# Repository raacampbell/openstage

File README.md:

<h1>OpenStage</h1>
<i>Open source microscope stage controller</i>
<br />

OpenStage is a hardware and software solution for cheaply motorizing a microscope stage. The system is accurate enough even for demanding tasks, such as fine focus operations on a 2-photon microscope. The characteristics of the system and important build information are described in our <a href="http://www.plosone.org/article/info%3Adoi%2F10.1371%2Fjournal.pone.0088977">PlosONE paper</a>. We achieved absolute unidirectional positioning accuracy and repeatability better than 0.1 μm in Z. Bidirectional positioning accuracy is in the range of 0.5 μm to 0.75 μm in Z. Positioning repeatability in X and Y is better than 1 μm. Minimum incremental motion is 0.04 μm in Z and 0.1 μm in X and Y. These values compare favorably to many commercial actuators costing several times as much as our system.

Our system costs roughly $1000 for three axes (controller + motors + motor coupling hardware). Up to four axes are possible. Commercial solutions cost in the region of $5,000 to $10,000. None of these costs include structural components such as bread-boards, linear translation stages, construction posts, etc, since all of this hardware is required no matter what motor solution is used. The breakdown of the costs is as follows:

* Motors and couplers are $100 to $200 per axis.
* Costs for micrometers, which act as the gear mechanism, are $80 to $150 per axis.
* A 4 axis controller unit can be assembled for under $500.

The cost savings come from the fact that we are using regular stepper motors instead of expensive linear actuators or servos. Further, the gears in our system are micrometers, which are easy to source and can even be bought at a discount from E-Bay. The main trade off compared to commercial systems is bulk, since connecting a stepper motor to a micrometer requires a relatively long (at least 8" or so) flexible shaft. However, if you can find a suitable leadscrew or rack and pinion gear as a substitute for the micrometer then the system will become more compact. A second trade off is that the controller unit does not have a feedback mechanism (encoders) for tracking position; position is inferred by counting the number of steps taken by the motors. In practice, this is not an issue as a properly assembled stage that is not driven beyond its operating limits will not lose position. Our system has maintained very high accuracy with zero maintanance. 

The stand-alone controller is based around an Arduino Mega. You can also build a single-axis controller around an Arduino Uno for under $100, but this can't accept a PS3 gamepad as there isn't sufficient SRAM on this device. The controller communicates with a PC via serial or virtual serial (USB) ports. An external LCD display and hand-held controller can also, optionally, be added. There is a PCB into which all components can easiliy be connected. The PCB was redesigned in Dec 2020 so that it's possible to construct it without obsolete SparkFun parts.  This verision of the PCB <a href="https://oshpark.com/shared_projects/8WlR0lh0">here</a> is no longer current. 

## Citing and Contact
Please do get in touch if you find this project useful or have used it in a publication. I'd love to hear from you!

## Updates

* *Arduino Mega ADK* - Users report that if the <a href="https://www.arduino.cc/en/Main/ArduinoBoardMegaADK">Arduino Mega ADK</a> is used, the project will run out of the box without the USB host shield.
* [Bluetooth gamepad connection details](https://github.com/raacampbell/openstage/issues/11#issuecomment-300612226)

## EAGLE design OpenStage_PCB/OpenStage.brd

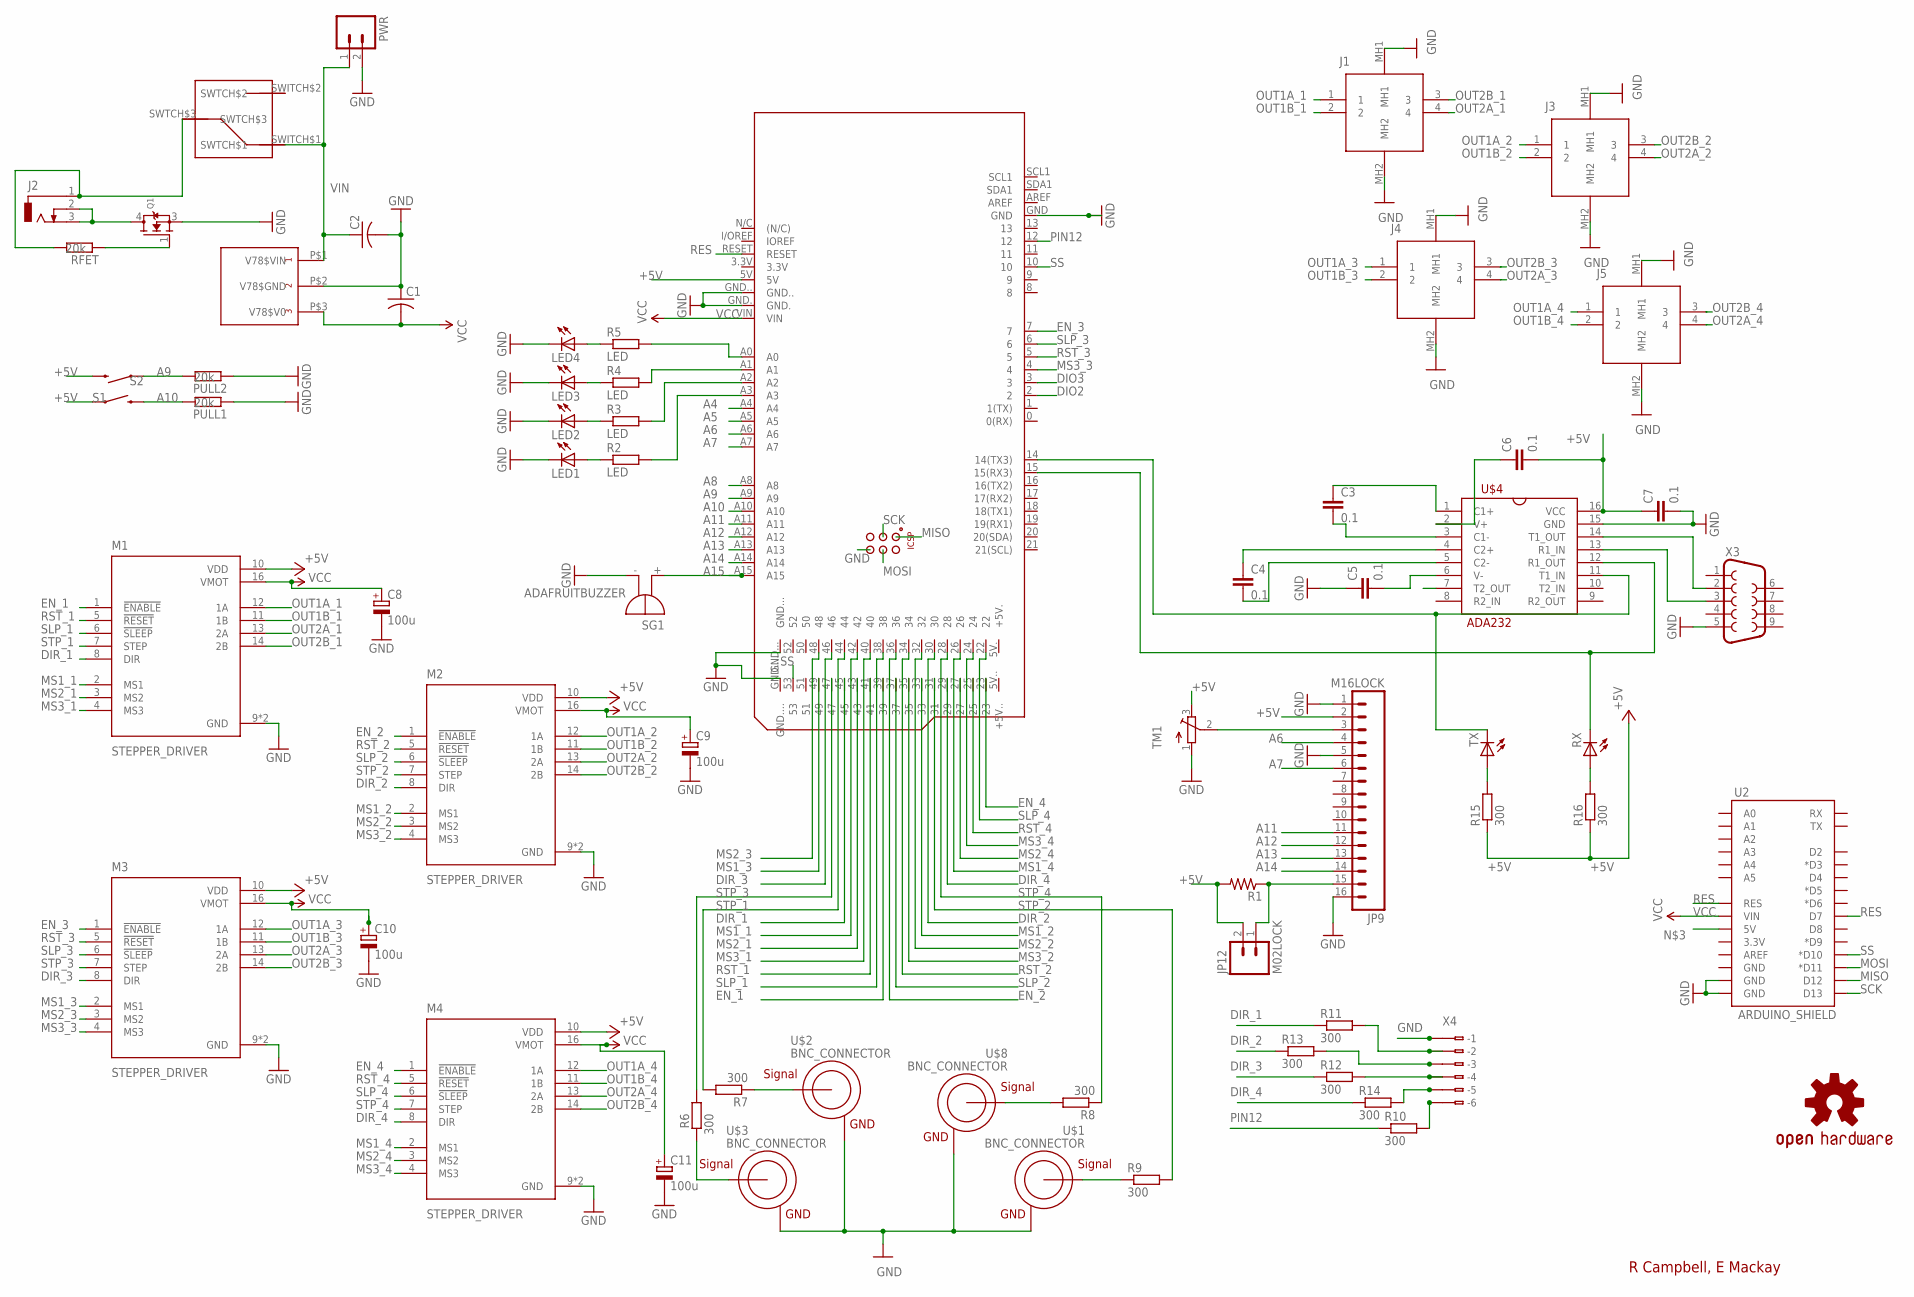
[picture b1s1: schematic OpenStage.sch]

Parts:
C1, C2: C-USC1210K; C1210K
C3, C4, C5, C6, C7: 0.1; AXIAL-5MM
C8, C9, C10, C11: 100u; E2,5-5
J1, J3, J4, J5: M8S-04PFFR-SF8001; M8S04PFFRSF8001
J2: DCJ0303
JP9: M16LOCK; 1X16_LOCK
JP12: M02LOCK; 1X02_LOCK
LED1, LED2, LED3, LED4: LED3MM
LOGO1: OSHW-LOGOL; OSHW-LOGO-L
M1, M2, M3, M4: STEPPER_DRIVER; POLOLU_CARRIER
PCB2: ARDUINO_MEGA_ROB
PULL1, PULL2: 20k; R3216
PWR: M02PTH; 1X02
Q1: MOSFET-N_TO252; TO252
R1: R-US_0204/7; 0204/7
R2, R3, R4, R5: LED; R3216
R6, R7, R8, R9, R10, R11, R12, R13, R14, R15, R16: 300; R3216
RFET: 20k; R3216
RX: LED3MM
S1, S2: SWITCH-MOMENTARY-212MM; TACTILE-PTH-12MM
SG1: ADAFRUITBUZZER; BMT1205XH7.5
TM1: TRIMPOT3386; TRIM-3386
TX: LED3MM
U2: ARDUINO_SHIELD; DUEMILANOVE_VIAS
U$1, U$2, U$3, U$8: BNC_CONNECTOR
U$4: ADA232; DIL16
U$5: V78XX-1000
U$6: SLIDING_SWITCH_0.185
X3: DB9FEMALE; DB9
X4: 233-206

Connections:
+5V: C6.P$2 (2), C7.P$1 (1), JP9.2, JP12.2, M1.10 (VDD), M2.10 (VDD), M3.10 (VDD), M4.10 (VDD), PCB2.5V, R1.2, R15.1, R16.1, S1.1, S2.3 (2), TM1.3 (E), U$4.16 (VCC)
A4: PCB2.A4
A5: PCB2.A5
A6: JP9.4, PCB2.A6
A7: JP9.6, PCB2.A7
A8: PCB2.A8
A9: PCB2.A9, PULL2.2, S2.1
A10: PCB2.A10, PULL1.2, S1.3 (2)
A11: JP9.11, PCB2.A11
A12: JP9.12, PCB2.A12
A13: JP9.13, PCB2.A13
A14: JP9.14, PCB2.A14
A15: PCB2.A15, SG1.+
DIO2: PCB2.2
DIO3: PCB2.3
DIR_1: M1.8 (DIR), PCB2.45, R11.1
DIR_2: M2.8 (DIR), PCB2.30, R13.1
DIR_3: M3.8 (DIR), PCB2.46, R12.1
DIR_4: M4.8 (DIR), PCB2.29, R14.1
EN_1: M1.1 (!ENABLE), PCB2.39
EN_2: M2.1 (!ENABLE), PCB2.36
EN_3: M3.1 (!ENABLE), PCB2.7
EN_4: M4.1 (!ENABLE), PCB2.23
GND: C1.1, C2.2, C5.P$1 (1), C7.P$2 (2), C8.-, C9.-, C10.-, C11.-, J1.MH1, J1.MH2, J3.MH1, J3.MH2, J4.MH1, J4.MH2, J5.MH1, J5.MH2, JP9.1, JP9.5, JP9.16, LED1.K (C), LED2.K (C), LED3.K (C), LED4.K (C), M1.9 (GND), M1.15 (GND), M2.9 (GND), M2.15 (GND), M3.9 (GND), M3.15 (GND), M4.9 (GND), M4.15 (GND), PCB2.GND, PCB2.GND., PCB2.GND.., PCB2.GND..., PCB2.GND...., PCB2.GND__, PULL1.1, PULL2.1, PWR.2, Q1.3 (S), SG1.-, TM1.1 (A), U2.GND@0 (GND), U2.GND@1 (GND), U$1.GND, U$2.GND, U$3.GND, U$4.15 (GND), U$5.P$2 (V78$GND), U$8.GND, X3.5, X4.B1 (B-1)
MISO: PCB2.MISO, U2.D12
MOSI: PCB2.MOSI, U2.D11 (*D11)
MS1_1: M1.2 (MS1), PCB2.42
MS1_2: M2.2 (MS1), PCB2.33
MS1_3: M3.2 (MS1), PCB2.49
MS1_4: M4.2 (MS1), PCB2.26
MS2_1: M1.3 (MS2), PCB2.43
MS2_2: M2.3 (MS2), PCB2.32
MS2_3: M3.3 (MS2), PCB2.48
MS2_4: M4.3 (MS2), PCB2.27
MS3_1: M1.4 (MS3), PCB2.40
MS3_2: M2.4 (MS3), PCB2.35
MS3_3: M3.4 (MS3), PCB2.4
MS3_4: M4.4 (MS3), PCB2.24
unnamed: R7.1, U$2.SIGNAL
unnamed: LED1.A, R2.1
unnamed: R9.1, U$1.SIGNAL
unnamed: LED2.A, R3.1
unnamed: LED3.A, R4.1
unnamed: LED4.A, R5.1
unnamed: PCB2.A0, R5.2
unnamed: PCB2.A1, R4.2
unnamed: PCB2.A2, R3.2
unnamed: PCB2.A3, R2.2
unnamed: JP9.15, JP12.1, R1.1
unnamed: PCB2.14 (14(TX3)), TX.K (C), U$4.11 (T1_IN)
unnamed: PCB2.15 (15(RX3)), RX.K (C), U$4.12 (R1_OUT)
unnamed: C3.P$1 (1), U$4.1 (C1+)
unnamed: C3.P$2 (2), U$4.3 (C1-)
unnamed: C4.P$1 (1), U$4.4 (C2+)
unnamed: C5.P$2 (2), U$4.6 (V-)
unnamed: C4.P$2 (2), U$4.5 (C2-)
unnamed: C6.P$1 (1), U$4.2 (V+)
unnamed: JP9.3, TM1.2 (S)
unnamed: U$4.13 (R1_IN), X3.3
unnamed: U$4.14 (T1_OUT), X3.2
unnamed: J2.1, RFET.2, U$6.SWTCH$3
unnamed: R8.2, U$8.SIGNAL
unnamed: R6.1, U$3.SIGNAL
unnamed: R11.2, X4.A2 (-2), X4.B2 (B-2)
unnamed: R12.2, X4.A4 (-4), X4.B4 (B-4)
unnamed: R13.2, X4.B3 (B-3)
unnamed: R14.2, X4.B5 (B-5)
unnamed: R10.2, X4.B6 (B-6)
unnamed: R15.2, TX.A
unnamed: R16.2, RX.A
unnamed: J2.2, J2.3, Q1.4 (D)
unnamed: Q1.1 (G), RFET.1
OUT1A_1: J1.1, M1.12 (1A)
OUT1A_2: J3.1, M2.12 (1A)
OUT1A_3: J4.1, M3.12 (1A)
OUT1A_4: J5.1, M4.12 (1A)
OUT1B_1: J1.2, M1.11 (1B)
OUT1B_2: J3.2, M2.11 (1B)
OUT1B_3: J4.2, M3.11 (1B)
OUT1B_4: J5.2, M4.11 (1B)
OUT2A_1: J1.4, M1.13 (2A)
OUT2A_2: J3.4, M2.13 (2A)
OUT2A_3: J4.4, M3.13 (2A)
OUT2A_4: J5.4, M4.13 (2A)
OUT2B_1: J1.3, M1.14 (2B)
OUT2B_2: J3.3, M2.14 (2B)
OUT2B_3: J4.3, M3.14 (2B)
OUT2B_4: J5.3, M4.14 (2B)
PIN12: PCB2.12, R10.1
RES: PCB2.RESET, U2.D7, U2.RES
RST_1: M1.5 (!RESET), PCB2.41
RST_2: M2.5 (!RESET), PCB2.34
RST_3: M3.5 (!RESET), PCB2.5
RST_4: M4.5 (!RESET), PCB2.25
SCK: PCB2.SCK, U2.D13
SLP_1: M1.6 (!SLEEP), PCB2.38
SLP_2: M2.6 (!SLEEP), PCB2.37
SLP_3: M3.6 (!SLEEP), PCB2.6
SLP_4: M4.6 (!SLEEP), PCB2.22
SS: PCB2.10, PCB2.53, U2.D10 (*D10)
STP_1: M1.7 (STEP), PCB2.44, R7.2
STP_2: M2.7 (STEP), PCB2.31, R9.2
STP_3: M3.7 (STEP), PCB2.47, R6.2
STP_4: M4.7 (STEP), PCB2.28, R8.1
VCC: C1.2, C8.+, C9.+, C10.+, C11.+, M1.16 (VMOT), M2.16 (VMOT), M3.16 (VMOT), M4.16 (VMOT), PCB2.VIN, U2.VIN, U$5.P$3 (V78$V0)
VIN: C2.1, PWR.1, U$5.P$1 (V78$VIN), U$6.SWITCH$1 (SWTCH$1)

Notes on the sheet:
R Campbell, E Mackay

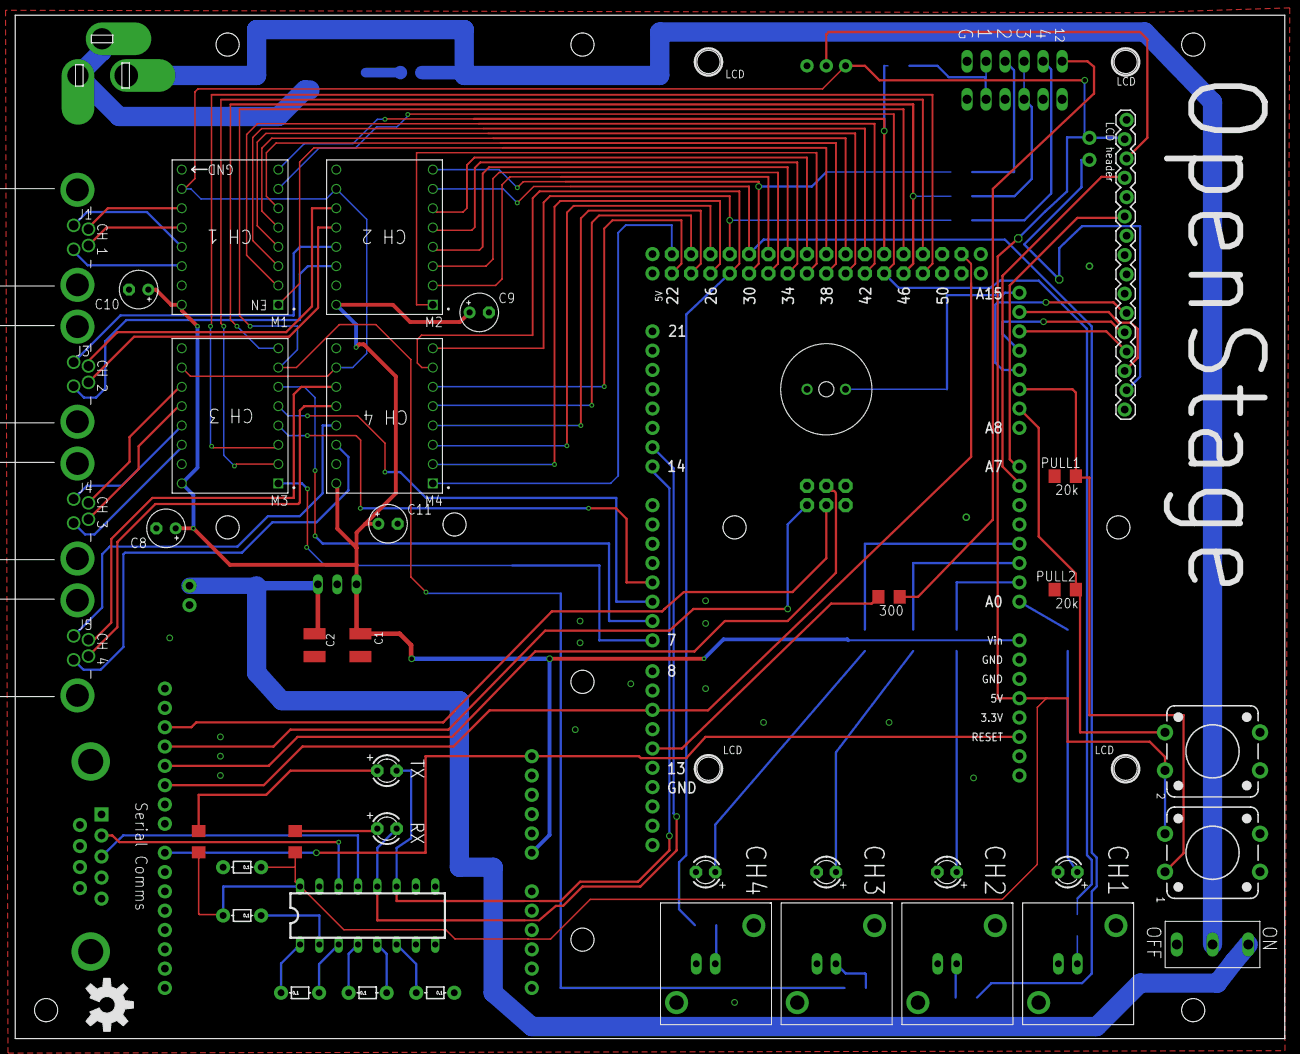
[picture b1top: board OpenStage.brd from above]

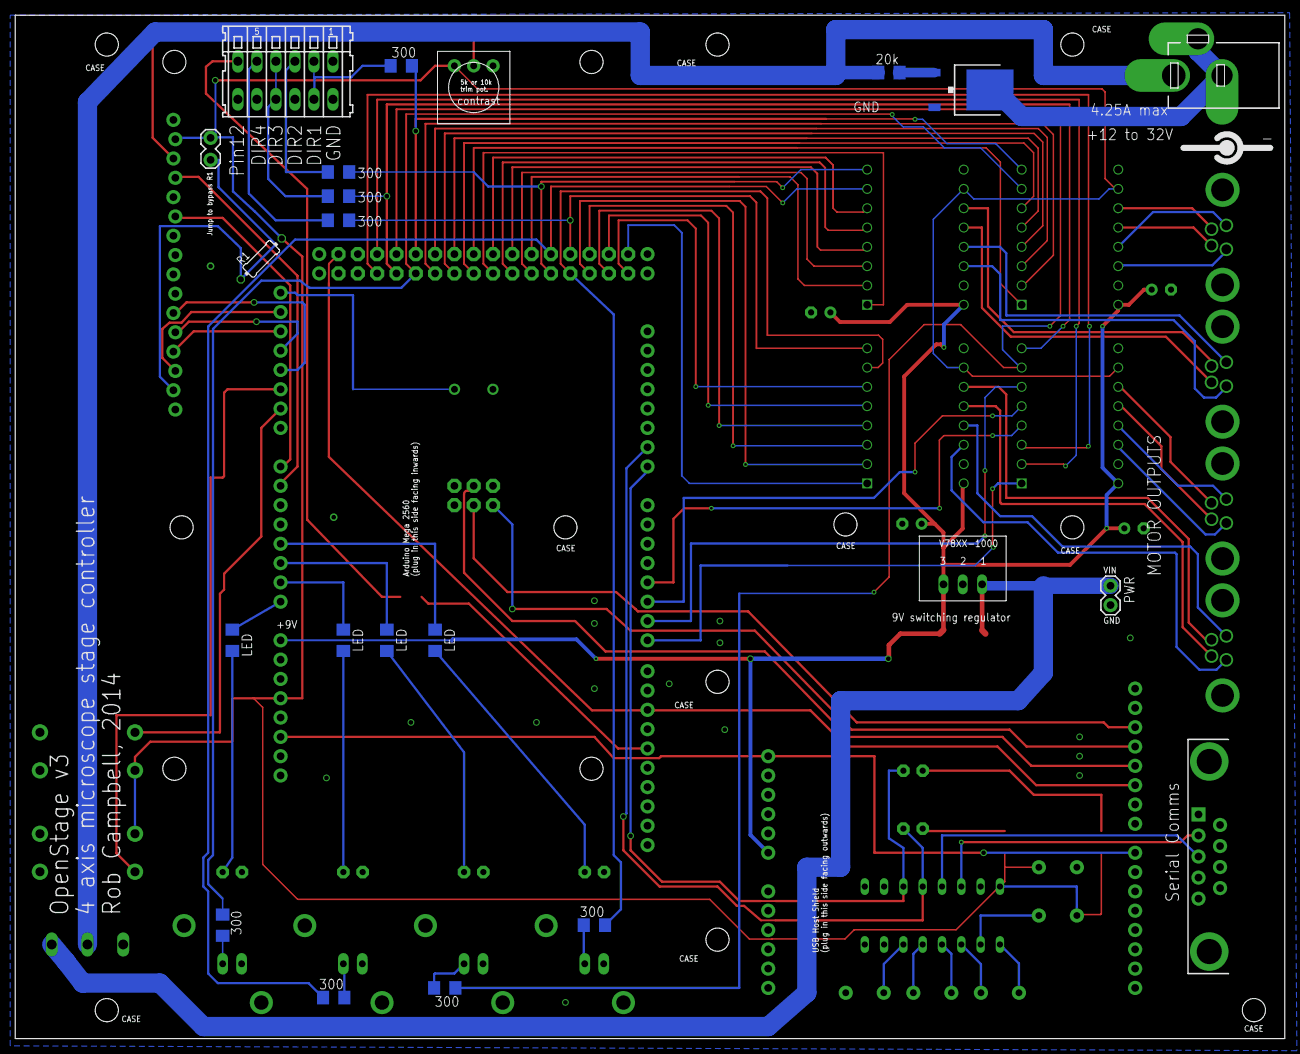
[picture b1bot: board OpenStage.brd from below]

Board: 2 copper layers, 167.0 x 134.6 mm, 65 parts (23 on the bottom side), 101 nets.

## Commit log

2013-09-10 modify README text
2014-03-05 minor comment change
2014-03-05 remove irrelevant stuff from some comments
2014-03-05 clarify a point in the comments
2014-03-05 move button timmers to OS_pollPS3.ino as static variables
2014-03-05 Add citation info
2014-03-05 Make warning info clearer
2014-03-11 Remove verbose flag
2014-03-11 typo
2014-03-25 remove comment line
2014-03-25 explain serial port in comments
2014-03-25 add parameter for disabling PS3 gamepad
2014-03-25 remove debug line
2014-03-25 add option to disable LCD display
2014-03-25 move some globals to statics in loop
2014-03-26 remove serial port reporting from setup()
2014-03-26 remove serial port reporting from pollPS3()
2014-03-26 remove serial port reporting
2014-03-26 remove serial port reporting from dButtonMove()
2014-03-26 expand readme file
2014-03-26 fix links
2014-04-08 update README.md with to do info.
2014-04-08 Add example Python and MATLAB serial control functions. Move Arduino (firmware) functions into their own directory.
2014-04-08 Add basic LabVIEW controller. This is just an example of what's possible, it's in no way fully featured or well coded.
2014-04-10 rename OpenStage directory and remove superflous Serial port commands.
2014-04-10 Create branch for developing the option to allow the USB port to be the serial control port.
2014-04-10 Remove commented line
2014-04-10 Don't print verbose information to USB if USB is being used to control stage.
2014-04-10 Remove USB serial print that was orphaned from some previous debugging attempt.
2014-04-10 Convert serial communications port to a pointer so we can easily switch between ports.
2014-04-10 Minor comment.
2014-04-10 Revert "Minor comment."
    This reverts commit 20cd1423a7b08549d447eb0300c777a8ea8039c5.
2014-04-10 Revert "Convert serial communications port to a pointer so we can easily switch between ports."
    This reverts commit 8afe9f7d0b82be5b729a1b7592cc51929de9a036.
2014-04-10 communicate via pointer to serial port
2014-04-10 controlling stage via USB is now verified to work
2014-04-10 controlViaUSB missing for some reason. Commits got buggered up for a bit. I think I didn't check out branch correctly.
2014-04-10 add missing declaration for a global pointer to HardwareSerial
2014-04-10 use #define for Serial1 (or whatever serial port we end up using)
2014-04-10 reorganize settings at top of main .INO
2014-04-10 Complete code reorganization to put all user-settable stuff into a single file.
2014-04-10 update serial port handling
2014-04-10 handle motion direction more gracefully to take into account users who don't have three channels.
2014-04-10 Settings back up file.
2014-04-10 Convert runSteppersToPos() to work with a variable number of axes. It's vitally important that this function works correctly.
2014-04-10 add warning comment.
2014-04-10 Modify MATLAB stage goto function to cope with arbitrary numbers of axes.
2014-04-10 Fix hideous bugs that caused new runSteppersToPos() code to not work.
2014-04-10 Fix speed issues with runSteppersToPos()
2014-04-10 Function wasn't sending terminal $ symbol.
2014-04-10 Largely working but takes a step each time it receives a serial port command. So if you repeatedly ask to go to the current position, the motor pulses along.
2014-04-11 Additional step bug fixed.
2014-04-11 Use preprocessor to optionally disable all traces of the LCD display.
2014-04-11 preprocessor stuff in settings file.
2014-04-11 Backup of settings files.
2014-04-11 Fix preprocessor syntax errors.
2014-04-11 Convert some ints to bytes
2014-04-11 settings change
2014-04-11 Changes to settings files. Single channel USB works on the Mega on the rig but not the Uno on the Mac. Move Uno to rig and try again.
2014-04-11 *WORKING* settings_Uno for 1 channel, no LCD, no PS3 gamepad
2014-04-11 Settings file for MEGA with three channels, PS3 gamepad, LCD display.
2014-04-11 remove unneeded settings file
2014-04-11 Allow OS_goto to automatically set the number of axes, but issue a warning when doing so.
2014-04-11 Create required Accelstepper instances dynamically when OpenStage boots.
2014-04-12 Update instructions and comments to provide more details on setting up a new system.
2014-04-12 Beep and report connection when MATLAB first links to stage.
2014-04-12 Remove if statement.
2014-04-12 Fix various bugs relating to enabling and disabling OpenStage settings.
2014-04-12 Add a default Mac/Unix and PC serial port address.
2014-04-12 Minor changes to settings files.
2014-04-12 Accidentally kept the old version of OpenStage.ino replacing with new version.
2014-04-12 Add a note that users must have version 1.37 or greater of AccelStepper.
2014-04-13 Update readme file to make OpenStage properties clearer.
2014-04-13 Improve build instructions for stage.
2014-04-17 correct minor typo
2014-04-17 Add verbose messages to setup()
2014-04-17 update settings file.
2014-04-17 Let's not mess with pin 13 by default
2014-04-17 add more verbose messages to setup
2014-04-17 replace speed mat calculation which got culled by mistake
2014-04-17 minor cosmetic changes to setup()
2014-04-17 changes to settings files
2014-04-17 Fix minor issues in settings file and update readme.
2014-04-18 Clarify that full steps can be problematic.
2014-04-18 Clarify that increasing current can reduce top speed.
2014-05-09 Add handshake because USB serial is slow and crappy on connecting with MATLAB.
2014-05-09 Fix bugs relating to virtual serial comms over USB
2014-05-15 Begin modifying code to accommodate the new PCB.
2014-05-15 Add loops to potentially handle separate micro-stepping on each channel. For now we simply set all channels to the same micro-step level. In the future we can easily modify the setStep function to al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
2014-05-29 Allow Triangle plus L/R to move 4th axis.
2014-05-29 Make it easier to set different numbers of axes and enable/disable axes.
2014-05-29 Set micro step pins more elegantly.
2014-05-29 Fix indexing bug for microstep pins.
2014-05-29 Set up PCB settings file.
2014-05-29 Add build instructions for PCB. Instructions also contain an outline for how to set up OpenStage, use the controller, MATLAB interfacing, and how to avoid motor skips, etc.
2014-05-30 Add parts list for PCB build.
2014-05-30 Add links to USB host shield and AccelStepper libraries.
2014-05-30 update title on read me
2014-05-30 Add image to readmd
2014-05-30 Modify readme
2014-05-30 make link pretty
2014-05-30 update read me.
2014-05-30 Modify license file. Add project name to the top.
2014-06-03 Highlight the importance of not ripping up traces on the Quadstepper when removing the power jack.
2014-06-04 Changes to getInfo message sent by stage to PC.
2014-06-04 Highlight the fact that pulse rate is limited.
2014-06-04 Add the facility to invert the directions of hat stick motions using code.
2014-06-04 Explain issues with stage speed.
2014-10-08 Trivial test commit. Add today's date to built notes.
2014-10-08 And revert that change to check if stuff is being cached.
2014-10-08 Highlight that it's the *stage* we're building.
2014-10-08 Remove newline.
2015-04-20 Update README.md
    pcb info
2015-06-05 Update URL for USB host shield in docs.
2015-06-05 Bug fix: with newer versions of the USB Host Shield we can't build unless SPI.h is explicitly included before PS3USB.h is included.
2015-06-05 add comment showing example of what the motion command will look like.
2015-09-21 Add missing variables to non-PCB settings files.
2015-09-21 Some timer-related code added to the main application, but not enough to get it to function.
2015-09-21 Add important testing function. This needs to work properly before we can finish adding the timers to the main code base.
2015-10-03 Add PCB files. These files should be for the corrected version (LCD and serial port not inverted).
2015-10-10 report that ADK will work instead of USB host shield
2016-08-13 Add accuracy figures to README
2017-05-10 Add info on how to connect using bluetooth
2017-07-11 add CAD files for thimble to shaft connection
2019-12-14 LGPL
2021-01-18 Replace quad-stepper board
2021-01-18 Generate gerbers for new PCB
2021-01-25 mention new PCB

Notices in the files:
parts and their libraries:
SparkFun-Connectors: Licensing: Creative Commons ShareAlike 4.0 International - https://creativecommons.org/licenses/by-sa/4.0
